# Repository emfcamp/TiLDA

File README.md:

TiLDA documentation
===================

This repository contains documentation, schematics, and libraries for use with TiLDA.
For example code, see the smaller "source" submodule.

Guides
======

* [Archived docs from 2012](http://wiki-archive.emfcamp.org/2012/articles/b/a/d/Badge.html)
* [Example source code](https://github.com/emfcamp/TiLDA-source)

* [Arduino Guide](http://arduino.cc/en/Guide/ArduinoLeonardo)
* [Getting started with the nRF24L01+](http://maniacbug.wordpress.com/2011/11/02/getting-started-rf24/)

Initialising
------------

    git clone --recursive https://github.com/emfcamp/TiLDA

or

    git clone git@github.com:emfcamp/TiLDA
    cd TiLDA
    git submodule update --init

For building instructions, please see the sample source submodule:

* [TiLDA-source](https://github.com/emfcamp/TiLDA-source)

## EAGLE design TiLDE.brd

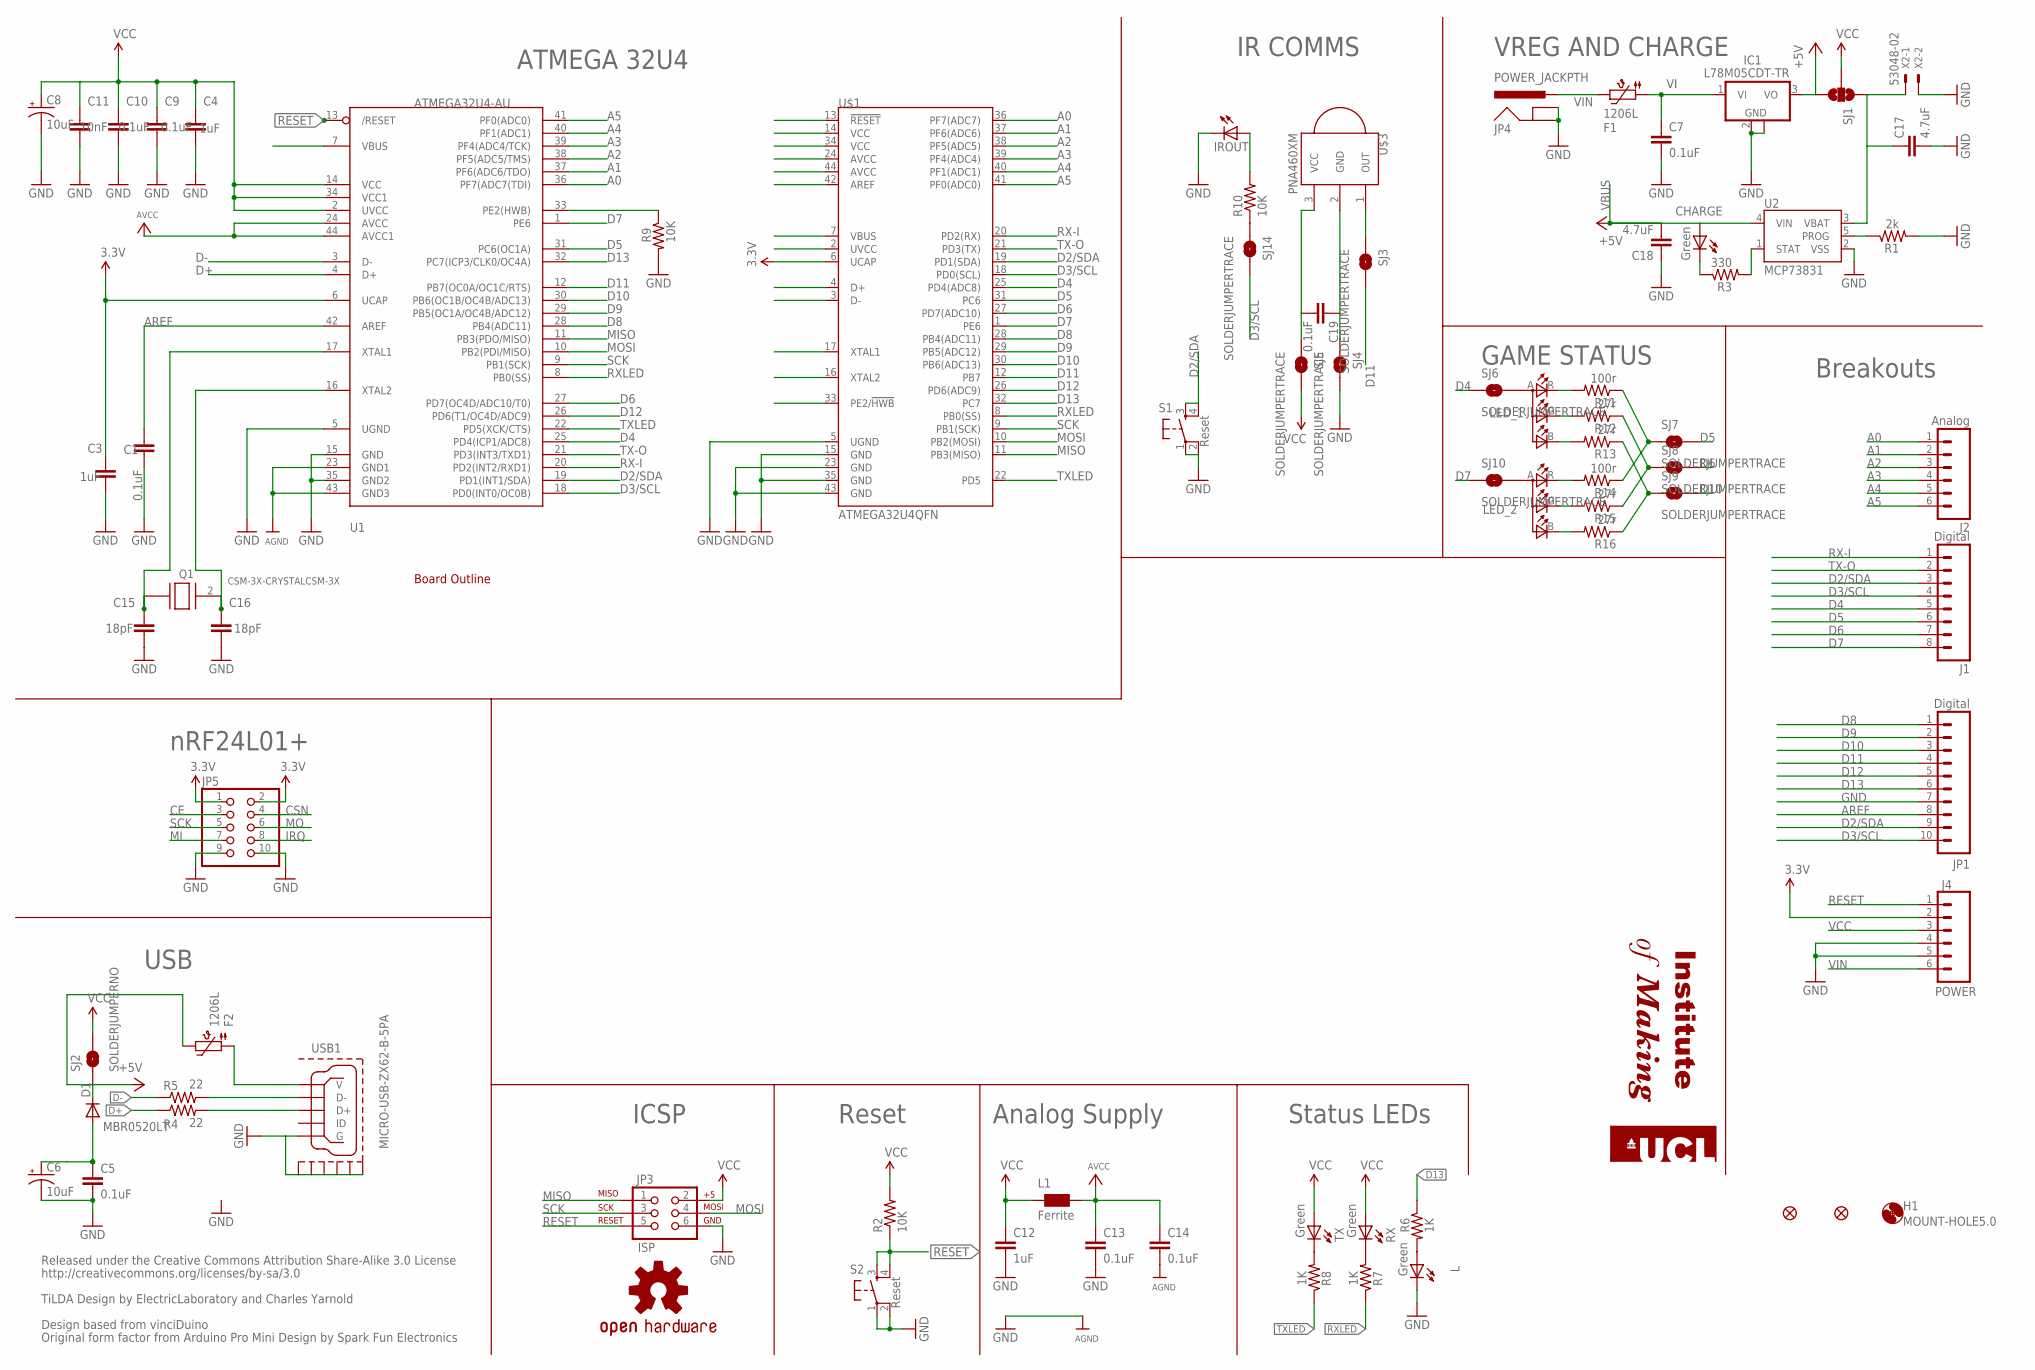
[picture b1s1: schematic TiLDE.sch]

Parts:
C1, C5, C7, C9, C10, C13, C14, C19: 0.1uF; C0603K
C3, C4, C12: 1uF; C0603K
C6, C8: 10uF; EIA3216
C11: 10nF; C0603K
C15, C16: 18pF; C0603K
C17, C18: 4.7uF; C0603K
CHARGE: Green; LED-1206
D1: MBR0520LT; SOD123
F1, F2: 1206L; 1206_PTC
H1: MOUNT-HOLE5.0; 5,0
IC1: L78M05CDT-TR; SOT-223-DPAK
IROUT: LED5MM
J1: Digital; 1X08
J2: Analog; 1X06
J4: POWER; 1X06
JP1: Digital; 1X10
JP2, JP6: FIDUCIAL1X2.5; FIDUCIAL-1X2.5
JP3: ISP; 2X3
JP4: POWER_JACKPTH; POWER_JACK_PTH
JP5: PINHD-2X5; 2X05
L: Green; LED-1206
L1: Ferrite; 1206W
LED_1, LED_2: CLV1A-FKB
Q1: CSM-3X-CRYSTALCSM-3X; CSM-3X
R1: 2k; 0603-RES
R2, R9, R10: 10K; 0603-RES
R3: 330; 0603-RES
R4, R5: 22; 0603-RES
R6, R7, R8: 1K; 0603-RES
R11, R14: 100r; 0603-RES
R12, R13, R15, R16: 27r; 0603-RES
RX: Green; LED-1206
S1, S2: Reset; TACTILE_SWITCH_SMD
SJ1: SOLDERJUMPER_2WAYT; SJ_2
SJ2: SOLDERJUMPERNO; SJ_2S-NO
SJ3, SJ4, SJ5, SJ6, SJ7, SJ8, SJ9, SJ10, SJ14: SOLDERJUMPERTRACE; SJ_2S-TRACE
TX: Green; LED-1206
U1: ATMEGA32U4-AU; TQFP44
U2: MCP73831; SOT23-5
U$1: ATMEGA32U4QFN; QFN-44
U$2: UCL-LOGO
U$3: PNA460XM
U$5: BOARDOUTLINE; BADGEBOARDBARE
U$14: OSHW-LOGOS; OSHW-LOGO-S
USB1: MICRO-USB-ZX62-B-5PA; ZX62-B-5PA
X2: 53048-02

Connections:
3.3V: C3.1, J4.2, JP5.1, JP5.2, U1.6 (UCAP), U$1.6 (UCAP)
+5V: IC1.3 (VO), SJ1.3
A0: J2.1, JP5.3, U1.36 (PF7(ADC7(TDI)), U$1.36 (PF7(ADC7))
A1: J2.2, JP5.4, U1.37 (PF6(ADC6/TDO)), U$1.37 (PF6(ADC6))
A2: J2.3, U1.38 (PF5(ADC5/TMS)), U$1.38 (PF5(ADC5))
A3: J2.4, U1.39 (PF4(ADC4/TCK)), U$1.39 (PF4(ADC4))
A4: J2.5, U1.40 (PF1(ADC1)), U$1.40 (PF1(ADC1))
A5: J2.6, U1.41 (PF0(ADC0)), U$1.41 (PF0(ADC0))
AREF: C1.2, JP1.8, U1.42 (AREF), U$1.42 (AREF)
AVCC: C13.1, C14.1, L1.2, U1.24 (AVCC), U1.44 (AVCC1), U$1.24 (AVCC), U$1.44 (AVCC)
D2: JP5.8
D2/SDA: J1.3, JP1.9, S1.3, S1.4, U1.19 (PD1(INT1/SDA)), U$1.19 (PD1(SDA))
D3/SCL: J1.4, JP1.10, SJ14.2, U1.18 (PD0(INT0/OC0B)), U$1.18 (PD0(SCL))
D4: J1.5, SJ6.1, U1.25 (PD4(ICP1/ADC8)), U$1.25 (PD4(ADC8))
D5: J1.6, SJ7.2, U1.31 (PC6(OC1A)), U$1.31 (PC6)
D6: J1.7, SJ8.2, U1.27 (PD7(OC4D/ADC10/T0)), U$1.27 (PD7(ADC10))
D7: J1.8, SJ10.1, U1.1 (PE6), U$1.1 (PE6)
D8: JP1.1, U1.28 (PB4(ADC11)), U$1.28 (PB4(ADC11))
D9: JP1.2, U1.29 (PB5(OC1A/OC4B/ADC12)), U$1.29 (PB5(ADC12))
D10: JP1.3, SJ9.2, U1.30 (PB6(OC1B/OC4B/ADC13)), U$1.30 (PB6(ADC13))
D11: JP1.4, SJ3.2, U1.12 (PB7(OC0A/OC1C/RTS)), U$1.12 (PB7)
D12: JP1.5, U1.26 (PD6(T1/OC4D/ADC9)), U$1.26 (PD6(ADC9))
D13: JP1.6, R6.1, U1.32 (PC7(ICP3/CLK0/OC4A)), U$1.32 (PC7)
D+: R4.1, U1.4 (D+), U$1.4 (D+)
D-: R5.1, U1.3 (D-), U$1.3 (D-)
GND: C1.1, C3.2, C4.2, C5.2, C6.C (-), C7.2, C8.C (-), C9.2, C10.2, C11.2, C12.2, C13.2, C14.2, C15.2, C16.2, C17.2, C18.1, IC1.2 (GND), IC1.4 (GND), IROUT.K (C), J4.4, J4.5, JP1.7, JP3.6, JP4.GND, JP4.GNDBREAK, JP5.9, JP5.10, L.C, R1.2, R9.2, S1.1, S1.2, S2.1, S2.2, SJ4.2, U1.5 (UGND), U1.15 (GND), U1.23 (GND1), U1.35 (GND2), U1.43 (GND3), U2.2 (VSS), U$1.5 (UGND), U$1.15 (GND), U$1.23 (GND), U$1.35 (GND), U$1.43 (GND), USB1.5 (G), USB1.GND@1 (GND1), USB1.GND@2 (GND2), USB1.GND@3 (GND3), USB1.GND@4 (GND4), USB1.GND@5 (GND5), USB1.GND@6 (GND6), X2.2
HWB: R9.1, U1.33 (PE2(HWB)), U$1.33 (PE2/!HWB)
MISO: JP3.1, JP5.7, U1.11 (PB3(PDO/MISO)), U$1.11 (PB3(MISO))
MOSI: JP3.4, JP5.6, U1.10 (PB2(PDI/MISO)), U$1.10 (PB2(MOSI))
unnamed: R8.2, TX.C
unnamed: R5.2, USB1.2 (D-)
unnamed: C19.1, SJ4.1, U$3.2 (GND)
unnamed: C19.2, SJ5.1, U$3.3 (VCC)
unnamed: R4.2, USB1.3 (D+)
unnamed: SJ3.1, U$3.1 (OUT)
unnamed: L.A, R6.2
unnamed: C17.1, SJ1.1, U2.3 (VBAT), X2.1
unnamed: R7.2, RX.C
unnamed: R1.1, U2.5 (PROG)
unnamed: R3.2, U2.1 (STAT)
unnamed: CHARGE.C, R3.1
unnamed: F2.1, USB1.1 (V)
unnamed: LED_1.R (CRED), R11.2
unnamed: LED_1.G (CGREEN), R12.2
unnamed: LED_1.B (CBLUE), R13.2
unnamed: LED_2.R (CRED), R14.2
unnamed: LED_2.G (CGREEN), R15.2
unnamed: LED_2.B (CBLUE), R16.2
unnamed: R11.1, R14.1, SJ7.1
unnamed: R12.1, R15.1, SJ8.1
unnamed: R13.1, R16.1, SJ9.1
unnamed: LED_2.A (ANODE), SJ10.2
unnamed: C5.1, C6.A (+), D1.A
unnamed: LED_1.A (ANODE), SJ6.2
unnamed: R10.1, SJ14.1
unnamed: IROUT.A, R10.2
RESET: J4.1, JP3.5, R2.1, S2.3, S2.4, U1.13 (/RESET), U$1.13 (!RESET)
RX-I: J1.1, U1.20 (PD2(INT2/RXD1)), U$1.20 (PD2(RX))
RXLED: R7.1, U1.8 (PB0(SS)), U$1.8 (PB0(SS))
SCK: JP3.3, JP5.5, U1.9 (PB1(SCK)), U$1.9 (PB1(SCK))
TX-O: J1.2, U1.21 (PD3(INT3/TXD1)), U$1.21 (PD3(TX))
TXLED: R8.1, U1.22 (PD5(XCK/CTS)), U$1.22 (PD5)
VBUS: C18.2, CHARGE.A, D1.C, F2.2, SJ2.1, U1.7 (VBUS), U2.4 (VIN), U$1.7 (VBUS)
VCC: C4.1, C8.A (+), C9.1, C10.1, C11.1, C12.1, J4.3, JP3.2, L1.1, R2.2, RX.A, SJ1.2, SJ2.2, SJ5.2, TX.A, U1.2 (UVCC), U1.14 (VCC), U1.34 (VCC1), U$1.2 (UVCC), U$1.14 (VCC), U$1.34 (VCC)
VI: C7.1, F1.1, IC1.1 (VI)
VIN: F1.2, J4.6, JP4.PWR
XTAL1: C15.1, Q1.1, U1.17 (XTAL1), U$1.17 (XTAL1)
XTAL2: C16.1, Q1.2, U1.16 (XTAL2), U$1.16 (XTAL2)

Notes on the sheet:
Released under the Creative Commons Attribution Share-Alike 3.0 License
http://creativecommons.org/licenses/by-sa/3.0
Original form factor from Arduino Pro Mini Design by Spark Fun Electronics
USB
Reset
ICSP
Analog Supply
Status LEDs
Breakouts
ATMEGA 32U4
Design based from vinciDuino
VREG AND CHARGE
SCK
CSN
IRQ
nRF24L01+
IR COMMS
GAME STATUS
TiLDA Design by ElectricLaboratory and Charles Yarnold
VBUS

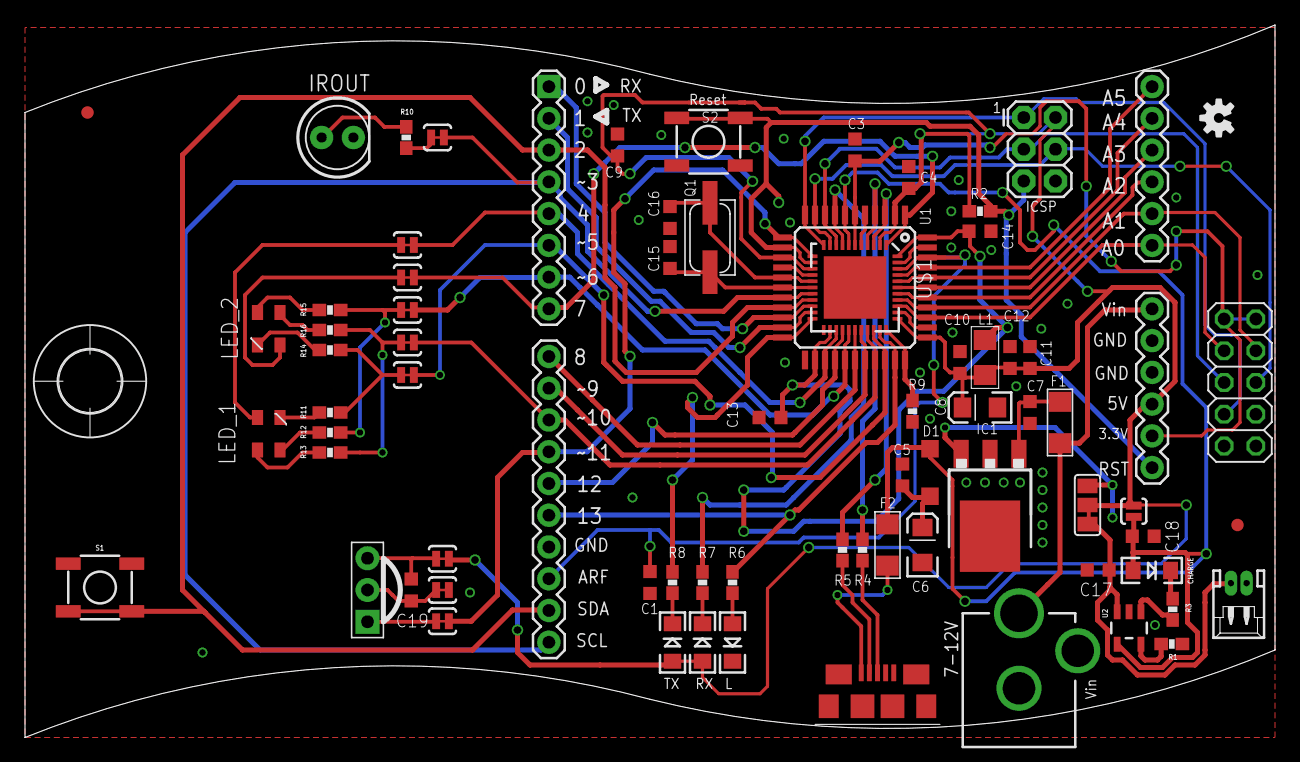
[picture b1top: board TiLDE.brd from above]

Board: 2 copper layers, 100.0 x 57.0 mm, 79 parts (1 on the bottom side), 67 nets.

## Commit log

2012-07-22 Add printouts
2012-07-26 change usb, fix silk screen, add ucl logo
2012-07-29 fix wireless MO and MI, remove un needed reset cap
2012-08-01 Fix routing under crystal
2012-08-02 add pdf layers
2012-08-02 update brd and sch pdfs
2012-08-19 Create schematics subdirectory
2012-08-19 Start adding datasheets
2012-08-19 .gitignore
2012-08-19 Wrong type of markdown
2012-08-19 More datasheets
2012-08-19 Add similar nRF24L01+ module
2012-08-25 Add RF24 library
2012-08-25 Add source submodule
2012-08-25 This should be the build process
2012-08-25 Using arduino.mk for now
2012-08-27 Update README and subproject for new Makefile
2012-08-27 Missing fi
2012-08-27 Let's not all run as root
2012-08-27 Not ideal
2012-09-01 Add Mirf library
2012-09-01 Added plan for badge program.
2012-09-01 compiling (but not working) copy of buildbrighton-ir-badge
2012-09-01 added some more test code
2012-09-01 eeprom code added, reqd libraries added
2012-09-01 simple 3-state torch mode added
2012-09-01 Added RGB example
2012-09-01 add RF24 code
2012-09-01 docs; fuckin about
2012-09-01 Adding RF lighting sync example
2012-09-01 brrroken rf24 recving
2012-09-02 moved from TiLDA-source
2012-09-02 Added more comments
2012-09-02 Adding 'white on startup'
2012-09-02 Removing red calibration, seems to stop red working
2012-09-02 Reenable debugging, add more colours
2012-09-02 remove empty source dir
2012-09-02 chroma: block while data is being sent
2012-09-02 colour repeater and client... almost working
2012-09-02 configure colour from makefile
2012-09-02 Modded lights lib to add non-blocking led_cycle
2012-09-02 Adding idle mode to badge
    Goes into cycle mode after 60 seconds of inactivity
2012-09-02 Clearer definitions, retabbed file
2012-09-02 Updating 55th flotilla readme
2012-09-02 Updating title in 55th readme
2012-09-02 make client peer to peer and poll for the button instead of using interrupts
2012-09-02 Changed the calibration, this fixes the chroma example
2012-09-02 red sort of works...
2012-09-02 roll back red changes
2012-09-02 fix stupid typeo
2012-09-02 I DON'T EVEN KNOW WHY THIS WORKS
2013-05-26 Moved to submodule (TiLDA-source)
2013-08-09 Revert "remove empty source dir"
    This reverts commit 6255e9b4216165383743836863cb688f24b1c151.
2013-08-09 Correct README
2013-08-09 Bring tested source up to date

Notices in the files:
parts and their libraries:
SparkFun-Passives: Licensing: CC v3.0 Share-Alike You are welcome to use this library for commercial purposes.
